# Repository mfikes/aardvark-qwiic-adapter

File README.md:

# aardvark-qwiic-adapter

Adapter from Total Phase Aardvark 10-pin connector to QWIIC pins, along with GPIO breakout

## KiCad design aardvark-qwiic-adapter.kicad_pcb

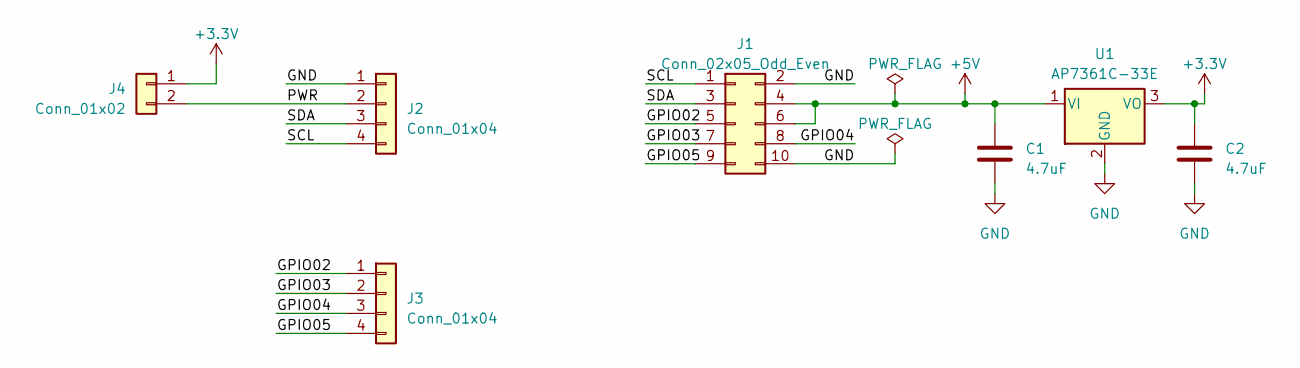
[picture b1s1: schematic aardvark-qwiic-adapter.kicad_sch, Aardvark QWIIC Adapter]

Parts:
C1, C2: 4.7uF; C_0805_2012Metric
J1: Conn_02x05_Odd_Even; PinHeader_2x05_P2.54mm_Vertical
J2: Conn_01x04; JST_SH_BM04B-SRSS-TB_1x04-1MP_P1.00mm_Vertical
J3: Conn_01x04; PinHeader_1x04_P2.54mm_Vertical
J4: Conn_01x02; PinHeader_1x02_P2.54mm_Vertical
U1: AP7361C-33E; SOT-223-3_TabPin2

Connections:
+3.3V: C2.1, J4.1, U1.3 (VO)
+5V: C1.1, J1.4, J1.6, U1.1 (VI)
/GPIO02: J1.5, J3.1
/GPIO03: J1.7, J3.2
/GPIO04: J1.8, J3.3
/GPIO05: J1.9, J3.4
/PWR: J2.2, J4.2
/SCL: J1.1, J2.4
/SDA: J1.3, J2.3
GND: C1.2, C2.2, J1.2, J1.10, J2.1, U1.2 (GND)

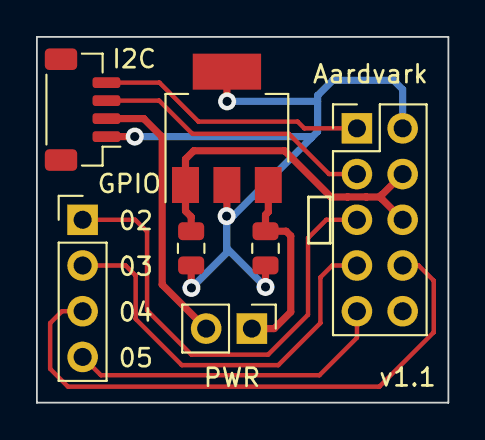
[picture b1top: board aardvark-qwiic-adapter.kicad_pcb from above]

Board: 2 copper layers, 22.9 x 20.3 mm, 7 parts (0 on the bottom side), 10 nets.

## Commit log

2023-02-19 Initial copy from Aardvark I2C breakout project
2023-02-19 Update README for project
2023-02-19 Remove I2C, relabel for GPIO
2023-02-19 Git ignore
2023-02-19 Room for labels
2023-02-19 Add LDO
2023-02-19 Caps on LDO
2023-02-19 QWIIC connector
2023-02-19 Title block
2023-02-19 GPIO breakout
2023-02-19 Power jumper
2023-02-19 Place components, 3d models
2023-02-19 Route
2023-02-19 Cleanup, title block
2023-02-19 Hide component names
2023-02-19 Connect +3.3V
2023-02-19 Move silkscreen to avoid DRC
2023-02-19 Ignore footprint DRC for JST connector
2023-02-19 PCB layout tweaks and silkscreen
2023-02-19 Clean up ground plance
2023-02-19 Tweak layout
2023-02-23 Fix backwards QWIIC
2023-02-23 Thicker power traces
